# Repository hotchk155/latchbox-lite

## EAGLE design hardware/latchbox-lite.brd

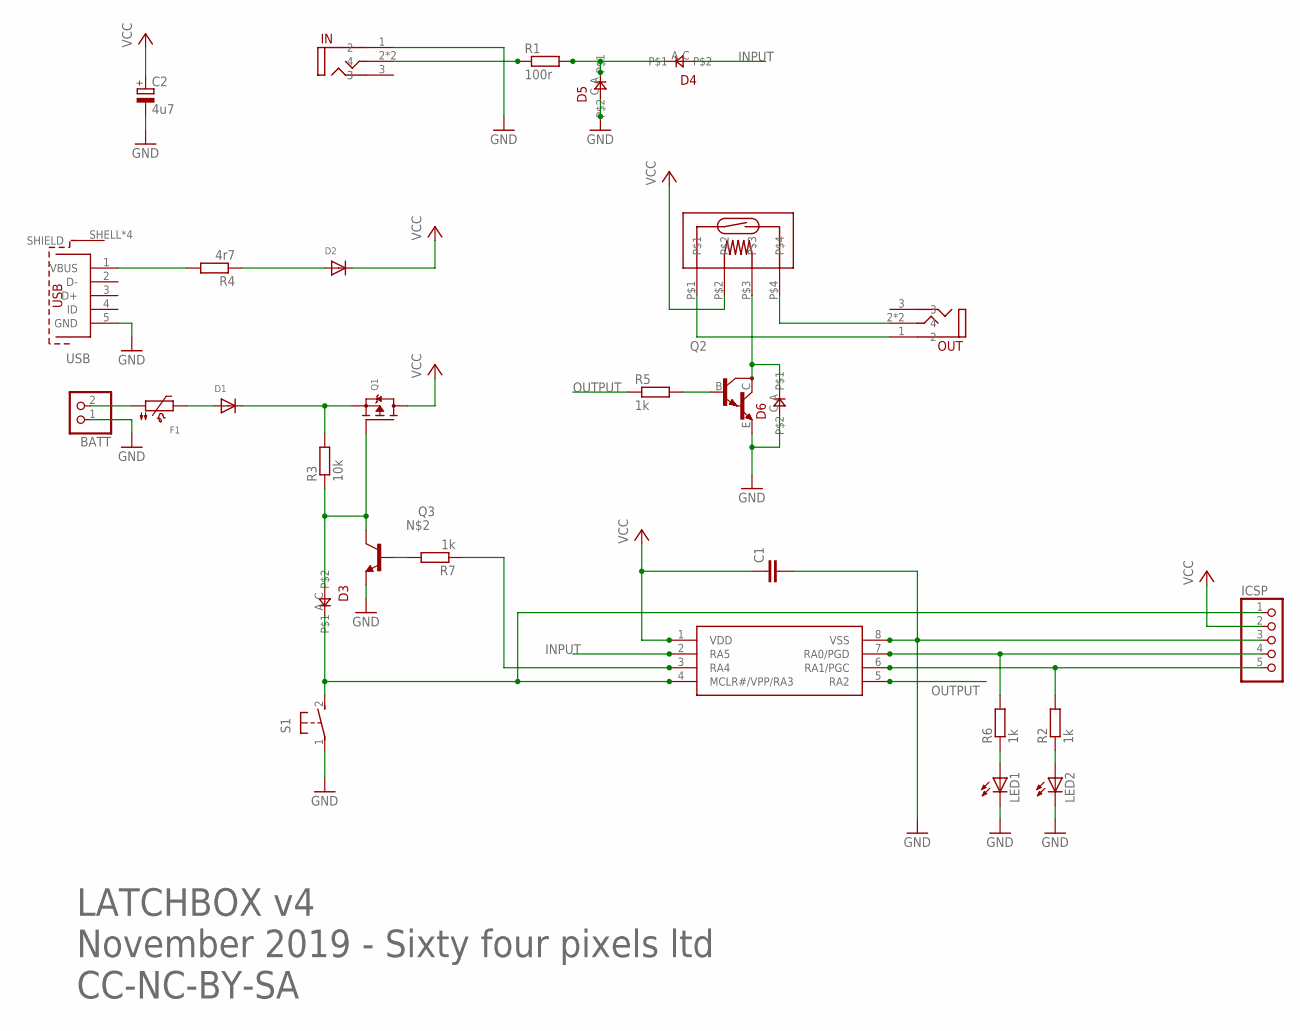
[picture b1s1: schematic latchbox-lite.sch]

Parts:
BATT: PINHD-1X2; 1X02
C1: C-EUC0805; C0805
C2: 4u7; E2,5-6E
D1, D2: DIODESOD-123; SOD-123
D3, D4, D5, D6: 0805DIODE
F1: PTC1206; 1206
IC1: PIC12F1822SO08; SO08
ICSP: PINHD-1X5; 1X05
IN: 3_5MM_PTH_MICRO
LED1, LED2: LED3MM
OUT: 3_5MM_PTH_MICRO
Q1: MOSFET-P; SOT23-R
Q2: MMBTA13LT1-NPN_DARL-SOT23-BEC; SOT23-BEC
Q3: MMBT3904LT1-NPN-SOT23-BEC; SOT23-BEC
R1: 100r; R0805
R2, R5, R6, R7: 1k; R0805
R3: 10k; R0805
R4: 4r7; R0805
RLY1: 9007-REED-RELAY
S1: 31-XX; B3F-31XX
USB: 629105150521

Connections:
GND: BATT.1, C1.2, C2.-, D5.C, D6.C, IC1.8 (VSS), ICSP.3, IN.1 (2), LED1.K (C), LED2.K (C), Q2.E, Q3.E, S1.1, USB.5 (GND)
INPUT: D4.C, IC1.2 (RA5)
unnamed: IN.2 (4), IN.2A (4), R1.1
unnamed: D3.C, Q1.1 (G), Q3.C, R3.1
unnamed: LED2.A, R2.1
unnamed: D1.C, Q1.2 (S), R3.2
unnamed: BATT.2, F1.1
unnamed: Q2.B, R5.2
unnamed: OUT.2 (4), OUT.2A (4), RLY1.P$4
unnamed: OUT.1 (2), RLY1.P$1
unnamed: D6.A, Q2.C, RLY1.P$3
unnamed: LED1.A, R6.1
unnamed: IC1.7 (RA0/PGD), ICSP.4, R6.2
unnamed: IC1.6 (RA1/PGC), ICSP.5, R2.2
unnamed: Q3.B, R7.2
unnamed: D3.A, IC1.4 (MCLR#/VPP/RA3), ICSP.1, S1.2 (S)
unnamed: D1.A, F1.2
unnamed: R4.2, USB.1 (VBUS)
OUTPUT: IC1.5 (RA2), R5.1
POWER_CTRL: IC1.3 (RA4), R7.1
USB_POWER: D2.A, R4.1
VCC: C1.1, C2.+, D2.C, IC1.1 (VDD), ICSP.2, Q1.3 (D), RLY1.P$2
Z: D4.A, D5.A, R1.2

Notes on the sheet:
LATCHBOX v4
November 2019 - Sixty four pixels ltd
CC-NC-BY-SA

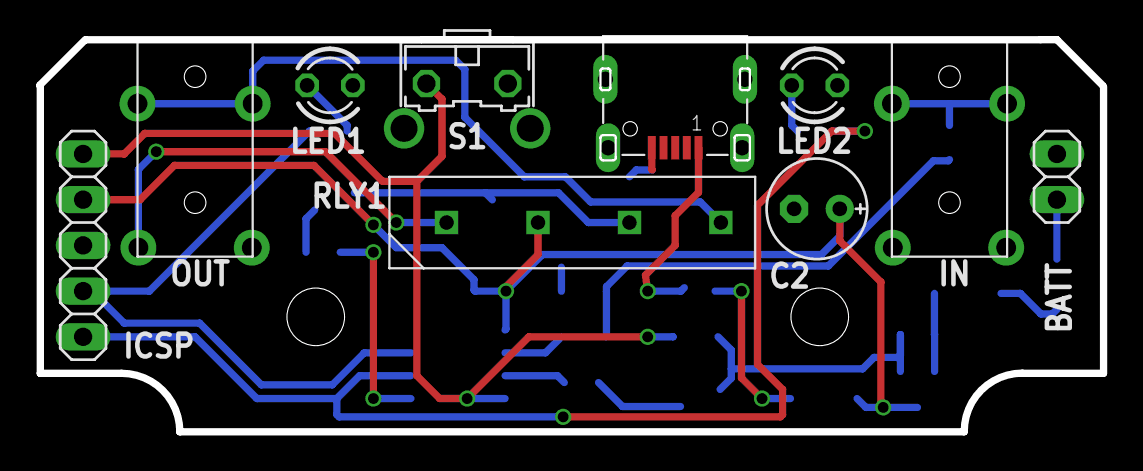
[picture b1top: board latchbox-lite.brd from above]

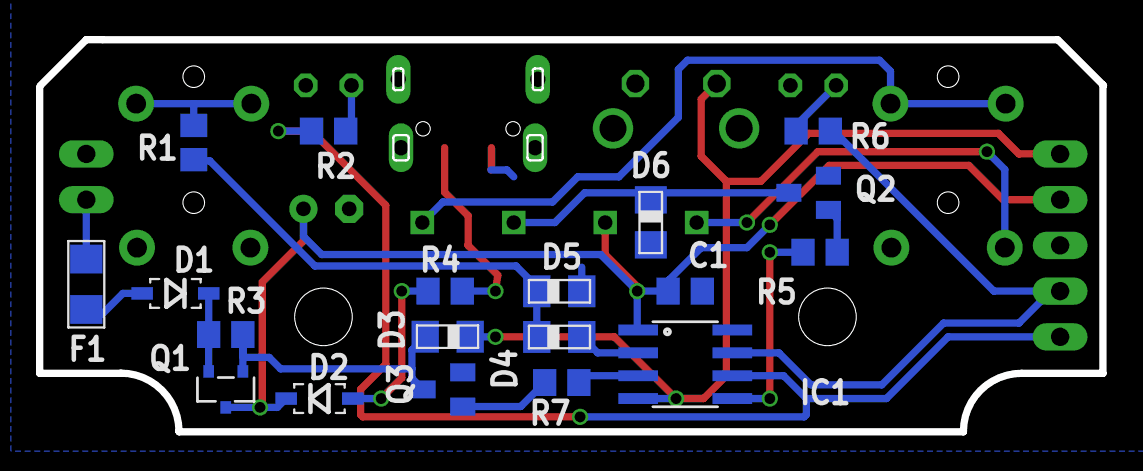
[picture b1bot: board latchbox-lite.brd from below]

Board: 2 copper layers, 59.1 x 21.8 mm, 29 parts (19 on the bottom side), 23 nets.

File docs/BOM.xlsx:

Reference | Description | Manufacturer | Supplier Ref
C1 | MC0805B104K250CT 100nF ceramic capacitor 0805 case | Multicomp | Farnell order code 2310668
C2 | 4.7uF 20% 50V 85°C 5mm electrolytic capacitor | Forever | Rapid order code 11-1522
D1, D2 | MBR0520LT1G schottky diode SOD-123 case | On Semi | Farnell order code 2317669
D3, D4, D5, D6 | TS4148 small signal diode 0805 case | Taiwan Semiconductor | Farnell order code 2839607
F1 | MC36207 PTC resettable fuse 30V/200mA 1206 case | Multicomp | Farnell order code 1861187
IC1 | PIC12F1822-I/SN microcontroller SOIC8 case | Microchip | Farnell order code 1971857
IN, OUT | MX-387GL 3.5mm Audio Connector | Pro Signal | Farnell order code 1267376
LED1 | 3501 3mm Red Diffused LED | Kitronic | Kitronic order code 3501
LED2 | 3565 Blue Diffused 3mm LED | Kitronic | Kitronic order code 3565
Q1 | IRLML2246TRPBF P channel MOSFET SOT-23 | Infineon | Farnell order code 1888166
Q2 | MMBTA13 NPN Darlington transistor SOT-23 | Fairchild | Farnell order code 9846590
Q3 | MMBT3904 NPN transistor SOT-23 | On Semi | Farnell order code 9846727
R1 | MC01W08051100R 100R 1% resistor 0805 case | Multicomp | Farnell order code 2129034
R2, R5, R6, R7 | MC01W080511K 1K 1% resistor 0805 case | Multicomp | Farnell order code 2129113
R3 | MC01W0805110K 10K 1% resistor 0805 case | Multicomp | Farnell order code 2129195
R4 | MC01W080514R7 4R7 1% resistor 0805 case | Multicomp | Farnell order code 9333304
RLY1 | Reed Relay 9007-05-01 5V, 500 ohm, 500 mA | Coto Technology | Farnell order code 1081622
S1 | SKHHLUA010 right angle tact switch 5.85mm stem | ALPS Alpine | RS Stock No. 758-2001
USB | 629105150521 micro USB connector | Wurth Electronic | Wurth part no. 629105150521
Reflow Solder Paste | Loctite GC 10 Lead Free Solder Paste | Henkel | RS order code 910-6790
Solder wire | 0.7mm Lead Free Solder Wire 0.5% Cu, 96.5% Sn, 3% Ag | RS Pro | RS order code 756-8884
Printed Circuit Board | Printed circuit board Pb free (custom design) | ALLPCB | custom
Front Panel | Laserables II acrylic laminate panel (custom laser cut) | Innovative Plastics | Hindleys SKU SUR1210

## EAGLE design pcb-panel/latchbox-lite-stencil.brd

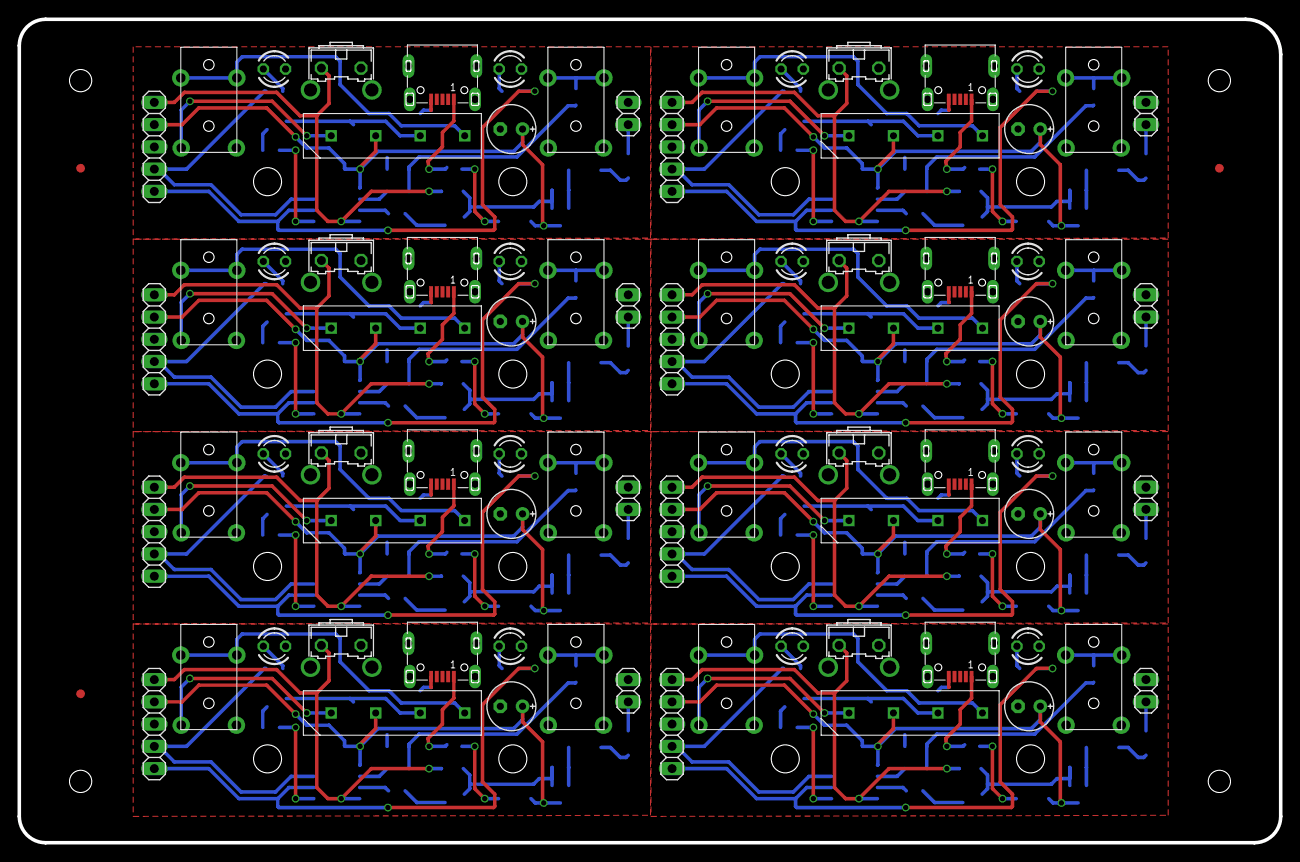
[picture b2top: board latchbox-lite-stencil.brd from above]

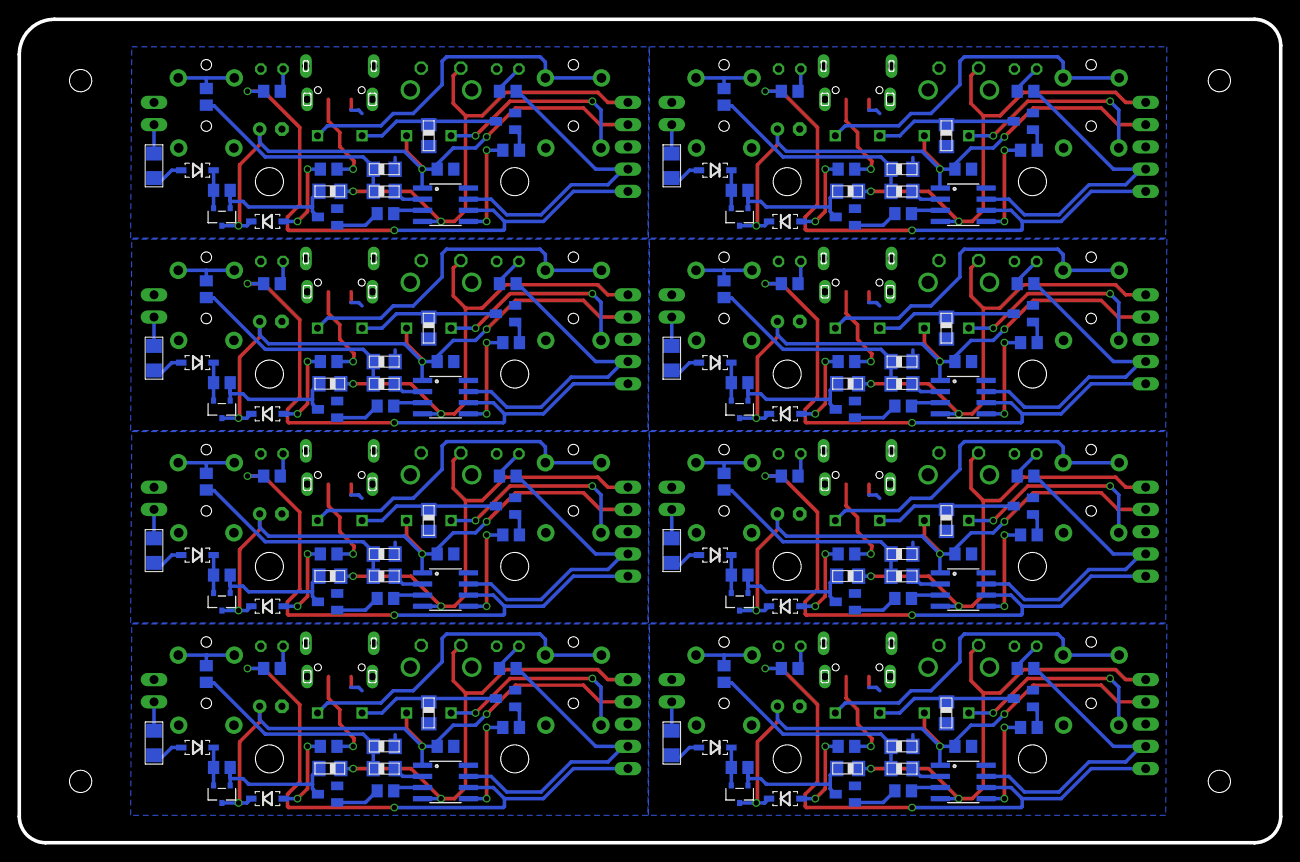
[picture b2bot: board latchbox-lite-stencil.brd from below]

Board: 2 copper layers, 144.0 x 94.0 mm, 235 parts (152 on the bottom side), 184 nets.

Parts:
BATT, BATT1, BATT2, BATT3, BATT4, BATT5, BATT6, BATT7: 1X02
C1, C3, C5, C7, C9, C11, C13, C15: C0805
C2, C4, C6, C8, C10, C12, C14, C16: 4u7; E2,5-6E
D1, D2, D9, D11, D15, D17, D21, D23, D27, D29, D33, D35, D39, D41, D45, D47: SOD-123
D3, D4, D5, D6, D7, D8, D10, D12, D13, D14, D16, D18, D19, D20, D22, D24, D25, D26, D28, D30, D31, D32, D34, D36, D37, D38, D40, D42, D43, D44, D46, D48: 0805DIODE
E$1, E$2, E$3: FIDUCIAL_1MM
F1, F2, F3, F4, F5, F6, F7, F8: 1206
IC1, IC2, IC3, IC4, IC5, IC6, IC7, IC8: PIC12F1822SO08; SO08
ICSP, ICSP1, ICSP2, ICSP3, ICSP4, ICSP5, ICSP6, ICSP7: 1X05
IN, IN1, IN2, IN3, IN4, IN5, IN6, IN7: 3_5MM_PTH_MICRO
LED1, LED2, LED3, LED4, LED5, LED6, LED7, LED8, LED9, LED10, LED11, LED12, LED13, LED14, LED15, LED16: LED3MM
OUT, OUT1, OUT2, OUT3, OUT4, OUT5, OUT6, OUT7: 3_5MM_PTH_MICRO
Q1, Q4, Q7, Q10, Q13, Q16, Q19, Q22: SOT23-R
Q2, Q3, Q5, Q6, Q8, Q9, Q11, Q12, Q14, Q15, Q17, Q18, Q20, Q21, Q23, Q24: SOT23-BEC
R1, R8, R15, R22, R29, R36, R43, R50: 100r; R0805
R2, R5, R6, R7, R9, R11, R12, R14, R16, R18, R19, R21, R23, R25, R26, R28, R30, R32, R33, R35, R37, R39, R40, R42, R44, R46, R47, R49, R51, R53, R54, R56: 1k; R0805
R3, R10, R17, R24, R31, R38, R45, R52: 10k; R0805
R4, R13, R20, R27, R34, R41, R48, R55: 4r7; R0805
RLY1, RLY2, RLY3, RLY4, RLY5, RLY6, RLY7, RLY8: 9007-REED-RELAY
S1, S2, S3, S4, S5, S6, S7, S8: B3F-31XX
USB, USB1, USB2, USB3, USB4, USB5, USB6, USB7: 629105150521

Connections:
GND: BATT.1, C1.2, C2.-, D5.C, D6.C, IC1.8, ICSP.3, IN.1, LED1.K, LED2.K, Q2.E, Q3.E, S1.1, USB.5
GND1: BATT1.1, C3.2, C4.-, D7.C, D8.C, IC2.8, ICSP1.3, IN1.1, LED3.K, LED4.K, Q5.E, Q6.E, S2.1, USB1.5
GND2: BATT2.1, C5.2, C6.-, D13.C, D14.C, IC3.8, ICSP2.3, IN2.1, LED5.K, LED6.K, Q8.E, Q9.E, S3.1, USB2.5
GND3: BATT3.1, C7.2, C8.-, D19.C, D20.C, IC4.8, ICSP3.3, IN3.1, LED7.K, LED8.K, Q11.E, Q12.E, S4.1, USB3.5
GND4: BATT4.1, C9.2, C10.-, D25.C, D26.C, IC5.8, ICSP4.3, IN4.1, LED9.K, LED10.K, Q14.E, Q15.E, S5.1, USB4.5
GND5: BATT5.1, C11.2, C12.-, D31.C, D32.C, IC6.8, ICSP5.3, IN5.1, LED11.K, LED12.K, Q17.E, Q18.E, S6.1, USB5.5
GND6: BATT6.1, C13.2, C14.-, D37.C, D38.C, IC7.8, ICSP6.3, IN6.1, LED13.K, LED14.K, Q20.E, Q21.E, S7.1, USB6.5
GND7: BATT7.1, C15.2, C16.-, D43.C, D44.C, IC8.8, ICSP7.3, IN7.1, LED15.K, LED16.K, Q23.E, Q24.E, S8.1, USB7.5
INPUT: D4.C, IC1.2
INPUT1: D10.C, IC2.2
INPUT2: D16.C, IC3.2
INPUT3: D22.C, IC4.2
INPUT4: D28.C, IC5.2
INPUT5: D34.C, IC6.2
INPUT6: D40.C, IC7.2
INPUT7: D46.C, IC8.2
unnamed: IN.2, IN.2A, R1.1
unnamed: D3.C, Q1.1, Q3.C, R3.1
unnamed: LED2.A, R2.1
unnamed: D1.C, Q1.2, R3.2
unnamed: BATT.2, F1.1
unnamed: Q2.B, R5.2
unnamed: OUT.2, OUT.2A, RLY1.P$4
unnamed: OUT.1, RLY1.P$1
unnamed: D6.A, Q2.C, RLY1.P$3
unnamed: LED1.A, R6.1
unnamed: IC1.7, ICSP.4, R6.2
unnamed: IC1.6, ICSP.5, R2.2
unnamed: Q3.B, R7.2
unnamed: D3.A, IC1.4, ICSP.1, S1.2
unnamed: D1.A, F1.2
unnamed: R4.2, USB.1
unnamed: IN1.2, IN1.2A, R8.1
unnamed: D9.C, Q4.2, R10.2
unnamed: BATT1.2, F2.1
unnamed: OUT1.2, OUT1.2A, RLY2.P$4
unnamed: OUT1.1, RLY2.P$1
unnamed: D8.A, Q5.C, RLY2.P$3
unnamed: D12.A, IC2.4, ICSP1.1, S2.2
unnamed: IC2.7, ICSP1.4, R11.2
unnamed: IC2.6, ICSP1.5, R12.2
unnamed: LED3.A, R12.1
unnamed: Q5.B, R9.2
unnamed: D9.A, F2.2
unnamed: R13.2, USB1.1
unnamed: LED4.A, R11.1
unnamed: D12.C, Q4.1, Q6.C, R10.1
unnamed: Q6.B, R14.2
unnamed: IN2.2, IN2.2A, R15.1
unnamed: D15.C, Q7.2, R17.2
unnamed: BATT2.2, F3.1
unnamed: OUT2.2, OUT2.2A, RLY3.P$4
unnamed: OUT2.1, RLY3.P$1
unnamed: D14.A, Q8.C, RLY3.P$3
unnamed: D18.A, IC3.4, ICSP2.1, S3.2
unnamed: IC3.7, ICSP2.4, R18.2
unnamed: IC3.6, ICSP2.5, R19.2
unnamed: LED5.A, R19.1
unnamed: Q8.B, R16.2
unnamed: D15.A, F3.2
unnamed: R20.2, USB2.1
unnamed: LED6.A, R18.1
unnamed: D18.C, Q7.1, Q9.C, R17.1
unnamed: Q9.B, R21.2
unnamed: IN3.2, IN3.2A, R22.1
unnamed: D21.C, Q10.2, R24.2
unnamed: BATT3.2, F4.1
unnamed: OUT3.2, OUT3.2A, RLY4.P$4
unnamed: OUT3.1, RLY4.P$1
unnamed: D20.A, Q11.C, RLY4.P$3
unnamed: D24.A, IC4.4, ICSP3.1, S4.2
unnamed: IC4.7, ICSP3.4, R25.2
unnamed: IC4.6, ICSP3.5, R26.2
unnamed: LED7.A, R26.1
unnamed: Q11.B, R23.2
unnamed: D21.A, F4.2
unnamed: R27.2, USB3.1
unnamed: LED8.A, R25.1
unnamed: D24.C, Q10.1, Q12.C, R24.1
unnamed: Q12.B, R28.2
unnamed: IN4.2, IN4.2A, R29.1
unnamed: D27.C, Q13.2, R31.2
unnamed: BATT4.2, F5.1
unnamed: OUT4.2, OUT4.2A, RLY5.P$4
unnamed: OUT4.1, RLY5.P$1
unnamed: D26.A, Q14.C, RLY5.P$3
unnamed: D30.A, IC5.4, ICSP4.1, S5.2
unnamed: IC5.7, ICSP4.4, R32.2
unnamed: IC5.6, ICSP4.5, R33.2
unnamed: LED9.A, R33.1
unnamed: Q14.B, R30.2
unnamed: D27.A, F5.2
unnamed: R34.2, USB4.1
unnamed: LED10.A, R32.1
unnamed: D30.C, Q13.1, Q15.C, R31.1
unnamed: Q15.B, R35.2
unnamed: IN5.2, IN5.2A, R36.1
unnamed: D33.C, Q16.2, R38.2
unnamed: BATT5.2, F6.1
unnamed: OUT5.2, OUT5.2A, RLY6.P$4
unnamed: OUT5.1, RLY6.P$1
unnamed: D32.A, Q17.C, RLY6.P$3
unnamed: D36.A, IC6.4, ICSP5.1, S6.2
unnamed: IC6.7, ICSP5.4, R39.2
unnamed: IC6.6, ICSP5.5, R40.2
unnamed: LED11.A, R40.1
unnamed: Q17.B, R37.2
unnamed: D33.A, F6.2
unnamed: R41.2, USB5.1
unnamed: LED12.A, R39.1
unnamed: D36.C, Q16.1, Q18.C, R38.1
unnamed: Q18.B, R42.2
unnamed: IN6.2, IN6.2A, R43.1
unnamed: D39.C, Q19.2, R45.2
unnamed: BATT6.2, F7.1
unnamed: OUT6.2, OUT6.2A, RLY7.P$4
unnamed: OUT6.1, RLY7.P$1
unnamed: D38.A, Q20.C, RLY7.P$3
unnamed: D42.A, IC7.4, ICSP6.1, S7.2
unnamed: IC7.7, ICSP6.4, R46.2
unnamed: IC7.6, ICSP6.5, R47.2
unnamed: LED13.A, R47.1
unnamed: Q20.B, R44.2
unnamed: D39.A, F7.2
unnamed: R48.2, USB6.1
unnamed: LED14.A, R46.1
unnamed: D42.C, Q19.1, Q21.C, R45.1
unnamed: Q21.B, R49.2
unnamed: IN7.2, IN7.2A, R50.1
unnamed: D45.C, Q22.2, R52.2
unnamed: BATT7.2, F8.1
unnamed: OUT7.2, OUT7.2A, RLY8.P$4
unnamed: OUT7.1, RLY8.P$1
unnamed: D44.A, Q23.C, RLY8.P$3
unnamed: D48.A, IC8.4, ICSP7.1, S8.2
unnamed: IC8.7, ICSP7.4, R53.2
unnamed: IC8.6, ICSP7.5, R54.2
unnamed: LED15.A, R54.1
unnamed: Q23.B, R51.2
unnamed: D45.A, F8.2
unnamed: R55.2, USB7.1
unnamed: LED16.A, R53.1
unnamed: D48.C, Q22.1, Q24.C, R52.1
unnamed: Q24.B, R56.2
OUTPUT: IC1.5, R5.1
OUTPUT1: IC2.5, R9.1
OUTPUT2: IC3.5, R16.1
OUTPUT3: IC4.5, R23.1
OUTPUT4: IC5.5, R30.1
OUTPUT5: IC6.5, R37.1
OUTPUT6: IC7.5, R44.1
OUTPUT7: IC8.5, R51.1
POWER_CTRL: IC1.3, R7.1
POWER_CTRL1: IC2.3, R14.1
POWER_CTRL2: IC3.3, R21.1
POWER_CTRL3: IC4.3, R28.1
POWER_CTRL4: IC5.3, R35.1
POWER_CTRL5: IC6.3, R42.1
POWER_CTRL6: IC7.3, R49.1
POWER_CTRL7: IC8.3, R56.1
USB_POWER: D2.A, R4.1
USB_POWER1: D11.A, R13.1
USB_POWER2: D17.A, R20.1
USB_POWER3: D23.A, R27.1
USB_POWER4: D29.A, R34.1
USB_POWER5: D35.A, R41.1
USB_POWER6: D41.A, R48.1
USB_POWER7: D47.A, R55.1
VCC: C1.1, C2.+, D2.C, IC1.1, ICSP.2, Q1.3, RLY1.P$2
VCC1: C3.1, C4.+, D11.C, IC2.1, ICSP1.2, Q4.3, RLY2.P$2
VCC2: C5.1, C6.+, D17.C, IC3.1, ICSP2.2, Q7.3, RLY3.P$2
VCC3: C7.1, C8.+, D23.C, IC4.1, ICSP3.2, Q10.3, RLY4.P$2
VCC4: C9.1, C10.+, D29.C, IC5.1, ICSP4.2, Q13.3, RLY5.P$2
VCC5: C11.1, C12.+, D35.C, IC6.1, ICSP5.2, Q16.3, RLY6.P$2
VCC6: C13.1, C14.+, D41.C, IC7.1, ICSP6.2, Q19.3, RLY7.P$2
VCC7: C15.1, C16.+, D47.C, IC8.1, ICSP7.2, Q22.3, RLY8.P$2
Z: D4.A, D5.A, R1.2
Z1: D7.A, D10.A, R8.2
Z2: D13.A, D16.A, R15.2
Z3: D19.A, D22.A, R22.2
Z4: D25.A, D28.A, R29.2
Z5: D31.A, D34.A, R36.2
Z6: D37.A, D40.A, R43.2
Z7: D43.A, D46.A, R50.2

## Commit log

2019-07-01 version 1 proto
2019-07-10 approvals
2019-07-24 prototype code
2019-07-24 tidy up da project
2019-08-17 v2 possible
2019-10-08 V3 BOARD
2019-10-25 V2 firmware
2019-11-06 move about
2019-11-06 V4 PANEL
2019-11-28 Version 3
2019-12-02 bom etc
2019-12-02 stencil
2021-07-28 panel.cdr
